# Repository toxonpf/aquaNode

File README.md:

# AquaNode website

React + TypeScript + Vite, React Router, React Three Fiber / Three.js and GSAP ScrollTrigger. Russian, English and Traditional Chinese (Taiwan) public interfaces; seven routes. Russian is the default. An icon-triggered language menu in the header and footer saves the selection and updates the interface without a reload. No contact form is configured.

## Run

Node 22.12+ (verified with Node 26) and npm:

```sh
npm install
npm run dev
```

Open the URL printed by Vite (normally http://127.0.0.1:5173).

```sh
npm run build
npm run preview
npx playwright test
```

Tests use Playwright Chromium (`npx playwright install chromium` if needed). An installed browser can be selected without editing the config:

```sh
PLAYWRIGHT_CHROMIUM_EXECUTABLE_PATH=/usr/bin/chromium npx playwright test
```

## Ocean styles

Open the browser developer console on the running site:

```js
oceanStyle(4)  // Select a style immediately, without reloading the scene.
oceanStyle(9)  // Return to the current ocean (default).
oceanStyle()   // List all styles with numbers, names and descriptions.
```

The choice is saved in this browser and survives reloads and navigation. The command is available on every page; the selected surface appears in the overview's 3D ocean. Static/reduced-motion illustrations remain static. Water, buoy motion and network links use the same selected wave profile. Invalid values throw a `RangeError` and leave the current choice unchanged.

| Number | Style | Version |
| --- | --- | --- |
| 1 | Original | Original fine sparkling ripples |
| 2 | Smooth | Softer surface before the depth refinements |
| 3 | Soft depth | Organic colour variation and soft highlights |
| 4 | Fine ripples | Previous lake-like directional ripples |
| 5 | Long swell | First long ocean swells |
| 6 | Broad foam | Long waves with wide foam patches |
| 7 | Crest ribbons | Narrow foam ribbons along crests |
| 8 | Textured crests | Four waves, deeper colour and broken foam |
| 9 | Ocean | Current six-wave ocean with large swells and sparse foam |

Preset definitions are in `src/features/ocean/scene/oceanStyles.ts`, the console command and saved choice in `src/features/ocean/scene/oceanStyle.ts`, shared CPU/GPU wave functions in `src/features/ocean/scene/ocean.ts`, and appearance variants in `src/features/ocean/scene/OceanSurface.tsx`. Historical variants reuse the current buoy model, rectangular float and underwater scene; the original style retains its historical circular waterline. Only the selected surface shader is compiled.

## Cursor styles

Switch immediately in the browser console; the selection is saved across pages and reloads:

```js
cursorStyle(0) // Native system cursor.
cursorStyle(1) // Water trail with animated arrows (default).
cursorStyle()  // Read the selected number.
```

The command is available on every page. Touch, reduced motion and forced colors retain native controls. The console store is in `src/features/cursor/cursorStyle.ts`; the pointer rendering is in `src/features/cursor/SiteCursor.tsx`.

## Future publication

Publish `dist/` as a static site after `npm run build`. Configure the host to serve `index.html` for application paths (`/about`, `/technology`, `/build`, `/journal`, `/team`); asset paths must serve the actual files. A Netlify-style `_redirects` file is included. No backend or secrets are required. Hosting and domain remain undecided; nothing has been published. Add the final absolute site URL and social preview image to the metadata when the domain is chosen.

## Editing

See the [project structure and editing map](docs/project-structure.md) for source folders, CSS order and test groups.

- `src/data/catalog.ts`: navigation, people and optional social links, resources, assembly steps, project updates, conceptual part descriptions.
- `src/main.tsx`: React startup; `src/app/App.tsx`: routes and page shell; `src/pages/`: page composition and English source phrases passed to `t()`.
- `src/data/content.ts`: localizes shared editorial records for the selected language.
- `src/features/i18n/i18n.ts` and `src/features/i18n/locales/ru*.ts` / `zh-TW.ts`: language selection, Russian copy and named placeholders. See [localization notes](docs/localization.md).
- `src/features/ocean/scene/Scene.tsx`: ocean rendering, lighting and camera transitions.
- `src/features/buoy/BuoyModel.tsx` and `src/features/buoy/BuoyDrawing.tsx`: lightweight 3D and static buoy illustrations, based on the supplied open-pisciculture reference.
- `src/features/ocean/story/BuoyAnnotation.tsx` and `src/features/buoy/buoyAnchors.ts`: the annotation's fixed attachment point, SVG arrow and damped bend. The 3D scene projects the lid point after applying the buoy's current wave transforms; only the bend has inertia, while the tip tracks exactly. The static illustration uses its corresponding SVG point.
- `src/features/ocean/story/SensorPanel.tsx`, `src/features/ocean/scene/Underwater.tsx` and `src/features/ocean/styles/sensors.css`: the underwater chapter, sensor explanations, projected probe controls, light and particles.
- `src/styles/base.css`: desktop and separately composed mobile layouts, reduced-motion rules.
- `public/resources/`: genuine supplied downloadable materials. Do not copy the entire engineering package into this public directory: it contains unapproved protocol details.
- `public/assets/`: supplied engineering images and licensed ocean recording.

New journal entries are objects in `updates`; leave dates undated when unknown. Team social links render only when a real `{ label, url }` item exists. Contacts and form work were explicitly deferred by the user; no email address or successful submission is fabricated.

## Design

The opening section is one full viewport of ocean viewed from above, with a cream and marine-blue buoy at its centre. A dark loading screen with a small spinner covers the scene until its first WebGL frame is rendered, then fades out over 900 ms to reveal the brighter ocean. The navigation sits over the water. One second after that reveal, “what is this?” fades in and a curved arrow draws toward the buoy. A moving line and downward arrow invite scrolling; both the annotation and cue link to the current project section. The rest of the overview remains available below while sections are refined individually.

The Three.js ocean uses an actual displaced mesh, analytic wave normals, reflected sky, sun glints and fine wind ripples. The buoy samples the same four directional swells as the water, so its height and tilt follow the surface. Wave parameters and the shared CPU/GPU equations are in `src/features/ocean/scene/ocean.ts`. Opening-section styles are in `src/features/ocean/styles/ocean.css`.

The opening has five chapters in one persistent canvas: the overhead surface, a close look at the buoy, and the probes below the water. Each distinct vertical wheel gesture, swipe or navigation key advances one adjacent chapter. Short anchors, 56–96 px apart, replace the empty viewport-length gaps. Further input is consumed until the camera and copy have settled and the current gesture has paused for 280 ms, preventing momentum from skipping a chapter. Leaving the last chapter returns to ordinary page scrolling; its remaining momentum is consumed until that gesture ends. Chapter links and the dive cue provide direct navigation. Pinch zoom, horizontal gestures and text/button input retain their normal controls. The underwater camera travels around and beneath the float; the background, underside of the water and light change with it. Text and its gradient appear together once the camera settles. The isolated pH, EC and temperature controls select a matching explanation, probe highlight and pulse colour. Moving labels attached to the probe array offer duplicate pointer controls; the stationary selector provides keyboard and screen-reader access. No live measurements are simulated. Reduced motion and unavailable WebGL retain all chapter navigation and sensor explanations with the static illustration.

No texture downloads or post-processing passes are used. The enclosure label is drawn locally on a small canvas. Animation runs only while the scene is visible and the browser tab is active. The secondary model renders on demand. Pending 3D uses a loading indicator rather than an SVG illustration. A static SVG is reserved for reduced motion, limited hardware, unavailable WebGL or a failed 3D download; those states leave loading immediately instead of waiting for a frame that cannot render. The buoy follows the open-pisciculture reference's rectangular float, central mast, upright enclosure and lower probe tube, with softened edges and an AquaNode finish. Its dimensions and details remain illustrative. Scrolling stays native.

## Evidence and unfinished content

Current engineering source: `AquaNode_R0.3_EC_pH_revC/`, dated 2 November 2026. revC is a freshwater bench configuration with experimental EC (SEN0244), temperature (DS18B20), and isolated pH (SEN0169-V2 → DFR0504 → ADS1115). The pH isolator uses a separate regulated bench supply; battery-powered pH and its energy budget are incomplete.

The supplied reports record 18 Python tests (15 EC model, 3 pH exporter), 166 schematic pins and 139 PCB pads compared across source files. These are source/software checks, not hardware evidence. Fifteen C++ pH assertions were not run. The ESP32 build attempt stopped during dependency download. Native ERC/DRC, physical calibration, shared-water tests and fabrication release remain pending. Real calibration coefficients and measured accuracy are not supplied. The presentation profile is simulation and is not used as hardware evidence.

`src/data/revisions/ec-ph-revc.json` is a website projection of these reports, with unknown outcomes kept null; it is not a supplied status file. `src/data/project.ts` exposes the current revision. RU/zh-TW revC copy is in `ru-revc.ts` and `zh-revc.ts`. Public summaries, status, evidence and attribution are under `public/resources/ec-ph-revc/`. Localized diagrams are generated by `scripts/design-architecture.mjs`. Firmware/protocol implementation is not added to web downloads. The supplied engineering directory is unchanged.

Historical revB downloads and diagrams remain at their existing URLs. Older R0.3 native checks and previous source counts are historical, not revC results. The independent Taiwan station archive and geographic map examples are not AquaNode field readings.

## Accessibility and loading

Model code is lazy-loaded, the secondary model waits for proximity to the viewport, and DPR is capped at 1.5. The hero animates only while visible in an active tab; secondary rendering uses demand mode. Reduced motion, data saver, limited reported memory, missing WebGL2 and lost contexts use a lightweight SVG view. Descriptions remain accessible without 3D. No automatic audio playback or audio download; one persistent toggle starts/stops the recording. Large imagery uses lazy loading. Native navigation, focus outlines, skip link, descriptive image alternatives and keyboard controls are present.

The 3D chunk still contains the Three.js renderer and is significantly larger than the core page. Users who request reduced motion or cannot use WebGL do not load it. Google Fonts uses display=swap with system fallbacks; the site is usable if fonts cannot load.

## Sources and licences

- Supplied `AquaNode_R0.3/`: README, Engineering, Purchase_and_test, Verification, BOM, Assembly and PCB drawings. Original directory is preserved. Public attribution: `public/resources/ATTRIBUTION.md`. New package documentation is CC BY 4.0; hardware CERN-OHL-P-2.0, with upstream notices in the original package.
- Award and historical context: https://thegeep.org/programs/youth-innovation-challenge/aquanode-team (checked 2026-10-21). Current user facts take precedence over its earlier capability description.
- Ocean audio: **Oceanwavescrushing.ogg**, Luftrum, 2008. https://commons.wikimedia.org/wiki/File:Oceanwavescrushing.ogg . Download: https://upload.wikimedia.org/wikipedia/commons/f/f1/Oceanwavescrushing.ogg . **CC BY 3.0**: https://creativecommons.org/licenses/by/3.0/ . Attribution and licence link appear in every page footer. The original file is unchanged; AquaNode applies a quieter mix and real-time underwater filtering. Playback is opt-in and limited to the five ocean chapters on the overview. Leaving the scene, changing page or hiding the tab fades and pauses it; returning resumes only if sound was enabled.
- Type: DM Sans and Manrope from Google Fonts, SIL Open Font License; https://fonts.google.com/specimen/DM+Sans and https://fonts.google.com/specimen/Manrope . Loaded from Google Fonts, not bundled.
- Design references reviewed: https://www.hut8.com (clear hierarchy and scale); https://15th.plus-ex.com (object-led reference, text access limited). https://encoder.digital/en was unavailable to the research tool; no claim of a completed visual review. No reference site's code or imagery was copied.
- Model and SVG fallback: authored for this website using the [open-pisciculture mechanical assembly and photographs](https://github.com/open-pisciculture/open-source-fish-farming-prototypes/tree/1ff67e96c81d22075cd6b9517ece5539700fd0e9/data-buoy-node) as visual references. The STEP assembly was reviewed; upstream meshes and photographs are not bundled. Source credits and adaptation details are in `public/resources/ATTRIBUTION.md`.

## Remaining user inputs

1. Real photographs of the working prototype and any existing full buoy assembly instructions (absent from the workspace).
2. Clarification of which board is used by the working buoy versus R0.3, and evidence the team wants to publish.
3. Real team portraits and contact addresses. Portrait slots and multiple contacts per person are ready; see [docs/team-contacts.md](docs/team-contacts.md). Unfilled contacts remain disabled.
4. Hosting and domain only when publication is requested.

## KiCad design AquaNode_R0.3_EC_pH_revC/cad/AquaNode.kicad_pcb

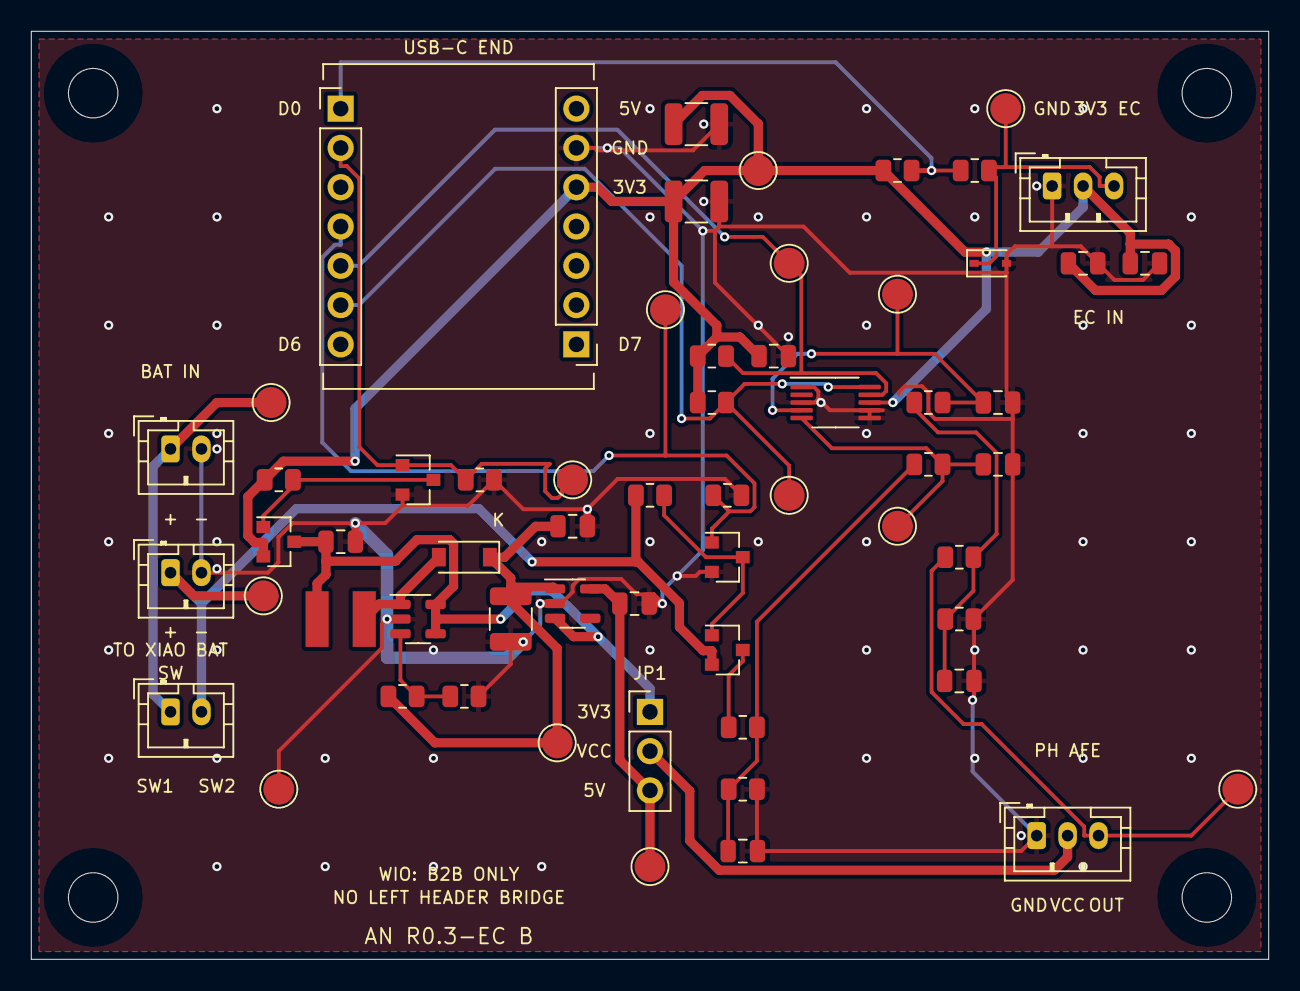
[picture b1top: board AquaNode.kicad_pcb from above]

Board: 2 copper layers, 80.0 x 60.0 mm, 65 parts (0 on the bottom side), 24 nets.

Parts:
C1, C13, C14, C15: 100nF; C_0805_2012Metric
C7, C10: 10uF; C_0805_2012Metric
C8, C17, C18: 22uF; C_1210_3225Metric
C9, C11, C12, C16: 1uF; C_0805_2012Metric
D1: Schottky 20V; D_SOD-123
D2: EC input ESD; D_SOD-323
H1, H2, H3, H4: M3 NPTH; MountingHole_3.2mm_M3
J1: XIAO_LEFT_D0..D6; PinHeader_1x07_P2.54mm_Vertical
J2: XIAO_RIGHT_D7..5V; PinHeader_1x07_P2.54mm_Vertical
J3: BATTERY + -; JST_PH_B2B-PH-K_1x02_P2.00mm_Vertical
J4: TO XIAO BAT PADS; JST_PH_B2B-PH-K_1x02_P2.00mm_Vertical
J5: SPST BATTERY SWITCH; JST_PH_B2B-PH-K_1x02_P2.00mm_Vertical
J7: EC G / 3V3-NO-CABLE / A; JST_PH_B3B-PH-K_1x03_P2.00mm_Vertical
J9: PH ISOLATED RETURN G / NC / A; JST_PH_B3B-PH-K_1x03_P2.00mm_Vertical
JP1: PH POWER 3V3 / 5V; PinHeader_1x03_P2.54mm_Vertical
L1: 10uH 1.4A sat; L_Bourns_SRN4018_Custom
Q1: P-MOS high side; SOT-23
Q2: N-MOS gate driver; SOT-23
Q3: Battery sense P-MOS; SOT-23
Q4: Battery sense driver; SOT-23
R1, R2: 4.7k; R_0805_2012Metric
R3: DNP - REMOVE 4.7k; R_0805_2012Metric
R4: 100R; R_0805_2012Metric
R5, R6, R18: 100k; R_0805_2012Metric
R7: 69.8k 0.1%; R_0805_2012Metric
R8: 20k 0.1%; R_0805_2012Metric
R9, R10: 49.9k 0.1%; R_0805_2012Metric
R11, R12: 100k 0.1%; R_0805_2012Metric
R15, R16: 1k; R_0805_2012Metric
R17: 1M; R_0805_2012Metric
TP1: VBAT_RAW; TestPoint_Pad_D2.0mm
TP2: VBAT; TestPoint_Pad_D2.0mm
TP3: 3V3; TestPoint_Pad_D2.0mm
TP4: BAT_EN; TestPoint_Pad_D2.0mm
TP5: 5V_PH; TestPoint_Pad_D2.0mm
TP6: GND; TestPoint_Pad_D2.0mm
TP7: I2C_SDA; TestPoint_Pad_D2.0mm
TP8: I2C_SCL; TestPoint_Pad_D2.0mm
TP9: EC_FILTERED; TestPoint_Pad_D2.0mm
TP10: PH_OUT; TestPoint_Pad_D2.0mm
TP11: PH_EN; TestPoint_Pad_D2.0mm
TP12: BOOST_RAW; TestPoint_Pad_D2.0mm
TP13: ADC_PH; TestPoint_Pad_D2.0mm
TP14: ADC_BAT; TestPoint_Pad_D2.0mm
U1: ADS1115; VSSOP-10_3x3mm_P0.5mm
U7: TPS61040; SOT-23-5
U8: 5V LDO; SOT-23-5

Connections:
3V3: C1.1, C15.1, C16.1, C17.1, C18.1, J2.5, J7.2, Q1.2, R1.1, R2.1, R3.1, R5.1, TP3.1, U1.8
5V_PH: C10.1, JP1.3, TP5.1, U8.5
ADC_BAT: C14.1, R16.2, TP14.1, U1.5
ADC_PH: C13.1, R15.2, TP13.1, U1.4
BAT_DIV: C12.1, R11.2, R12.1, R16.1
BAT_EN: J1.4, Q4.1, R18.1, TP4.1
BAT_GATE: Q3.1, Q4.3, R17.2
BAT_SENSE: Q3.3, R11.1
BOOST_FB: R7.2, R8.1, U7.3
BOOST_IN: C7.1, JP1.1, L1.1, Q1.3, U7.4, U7.5, U8.3
BOOST_RAW: C8.1, C9.1, D1.1, R7.1, TP12.1, U8.1
BOOST_SW: D1.2, L1.2, U7.1
EC_ADC: J1.1, R3.2, R4.1
EC_FILTERED: D2.1, J7.3, R4.2, TP9.1
GND: C1.2, C7.2, C8.2, C9.2, C10.2, C11.2, C12.2, C13.2, C14.2, C15.2, C16.2, C17.2, C18.2, D2.2, J2.6, J3.2, J4.2, J7.1, J9.1, Q2.2, Q4.2, R6.2, R8.2, R10.2, R12.2, R18.2, TP6.1, U1.1, U1.3, U1.6, U1.7, U7.2, U8.2
I2C_SCL: J1.6, R2.2, TP8.1, U1.10
I2C_SDA: J1.5, R1.2, TP7.1, U1.9
PH_DIV: C11.1, R9.2, R10.1, R15.1
PH_EN: J1.2, Q2.1, R6.1, TP11.1
PH_GATE: Q1.1, Q2.3, R5.2
PH_OUT: J9.3, R9.1, TP10.1
PH_SUPPLY: J9.2, JP1.2
VBAT: J4.1, J5.2, Q3.2, R17.1, TP2.1
VBAT_RAW: J3.1, J5.1, TP1.1

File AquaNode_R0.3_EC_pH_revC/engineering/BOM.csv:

reference,value,mpn,location,fit,notes
J1,XIAO_LEFT_D0..D6,Samtec TSW-107-07-G-S,carrier,FIT,D0/GPIO1 EC ADC; D6/GPIO43 DS18B20. USB CDC only; do not use UART0 TX.
J2,XIAO_RIGHT_D7..5V,Samtec TSW-107-07-G-S,carrier,FIT,Pin 7 at USB end. USB_DEV is XIAO 5V/VBUS; never inject boosted power.
J3,BATTERY + -,B2B-PH-K-S(LF)(SN),carrier,FIT,Protected 1S pack only. Verify actual plug polarity; JST housing does not guarantee polarity.
J4,TO XIAO BAT PADS,B2B-PH-K-S(LF)(SN),carrier,FIT,Pigtail soldered to XIAO underside BAT+/BAT- pads. Not to 3V3 or 5V.
J5,SPST BATTERY SWITCH,B2B-PH-K-S(LF)(SN),carrier,FIT,External two-wire SPST. USB remains a service power source; unplug USB for full shutdown.
J7,EC G / 3V3-NO-CABLE / A,B3B-PH-K-S(LF)(SN),carrier,FIT,"Pin 2 remains 3V3 copper. Depopulate and insulate cable contact 2. SEN0244 VCC comes from TP5, never bridge TP5 to J7.2."
J9,PH ISOLATED RETURN G / NC / A,B3B-PH-K-S(LF)(SN),carrier,FIT,J9.1 MCU GND; J9.2 NO CABLE CONTACT; J9.3 DFR0504 MCU A. JP1 shunt removed. SEN0169-V2 connects ONLY to isolated SEN side of M4.
JP1,PH POWER 3V3 / 5V,Samtec TSW-103-07-G-S,carrier,FIT,NO SHUNT in revC. Both 1-2 and 2-3 forbidden for this harness; J9.2 has no cable contact.
U1,ADS1115,ADS1115IDGSR,carrier,FIT,"0x48; AIN0 pH via original 49.9k/49.9k divider; single-shot +/-4.096V, 16 SPS. AIN2/3 grounded."
U7,TPS61040,TPS61040DBVR,carrier,FIT,EN tied to switched input to avoid EN > VIN during power-off.
U8,5V LDO,TPS7A2050PDBVR,carrier,FIT,EN follows switched boost input; check startup and shutdown transients.
Q1,P-MOS high side,AO3401A,carrier,FIT,
Q2,N-MOS gate driver,"2N7002,215",carrier,FIT,
D1,Schottky 20V,MBR0520LT1G,carrier,FIT,
D2,EC input ESD,"PESD3V3S1BA,115",carrier,FIT,"ESD only; leakage/clamp require bench verification, not powered-off isolation."
L1,10uH 1.4A sat,SRN4018-100M,carrier,FIT,"Semi-shielded; land pattern from Bourns recommended layout, still requires CAD review."
R1,4.7k,CRCW08054K70FKEA,carrier,FIT,
R2,4.7k,CRCW08054K70FKEA,carrier,FIT,
R3,DNP - REMOVE 4.7k,CRCW08054K70FKEA,carrier,DNP,Mandatory removal; otherwise biases EC analog input.
R4,100R,CRCW0805100RFKEA,carrier,FIT,
R5,100k,CRCW0805100KFKEA,carrier,FIT,
R6,100k,CRCW0805100KFKEA,carrier,FIT,
R7,69.8k 0.1%,RNCS0805BKE69K8,carrier,FIT,
R8,20k 0.1%,RT0805BRD0720KL,carrier,FIT,
R9,49.9k 0.1%,RT0805BRD0749K9L,carrier,FIT,
R10,49.9k 0.1%,RT0805BRD0749K9L,carrier,FIT,
R11,100k 0.1%,RT0805BRD07100KL,carrier,FIT,
R12,100k 0.1%,RT0805BRD07100KL,carrier,FIT,
R15,1k,CRCW08051K00FKEA,carrier,FIT,
R16,1k,CRCW08051K00FKEA,carrier,FIT,
C1,100nF,GRM21BR71H104KA01L,carrier,FIT,
C7,10uF,GRM21BR61A106KE19L,carrier,FIT,
C8,22uF,GRM32ER71C226KEA8L,carrier,FIT,
C9,1uF,GRM21BR71E105KA99L,carrier,FIT,
C10,10uF,GRM21BR61A106KE19L,carrier,FIT,
C11,1uF,GRM21BR71E105KA99L,carrier,FIT,
C12,1uF,GRM21BR71E105KA99L,carrier,FIT,
C13,100nF,GRM21BR71H104KA01L,carrier,FIT,
C14,100nF,GRM21BR71H104KA01L,carrier,FIT,
C15,100nF,GRM21BR71H104KA01L,carrier,FIT,
C16,1uF,GRM21BR71E105KA99L,carrier,FIT,
C17,22uF,GRM32ER71C226KEA8L,carrier,FIT,
C18,22uF,GRM32ER71C226KEA8L,carrier,FIT,
TP1,VBAT_RAW,PCB copper pad,carrier,FIT,No purchased component.
TP2,VBAT,PCB copper pad,carrier,FIT,No purchased component.
TP3,3V3,PCB copper pad,carrier,FIT,No purchased component.
TP4,BAT_EN,PCB copper pad,carrier,FIT,No purchased component.
TP5,5V_PH,PCB copper pad,carrier,FIT,No purchased component.
TP6,GND,PCB copper pad,carrier,FIT,No purchased component.
TP7,I2C_SDA,PCB copper pad,carrier,FIT,No purchased component.
TP8,I2C_SCL,PCB copper pad,carrier,FIT,No purchased component.
TP9,EC_FILTERED,PCB copper pad,carrier,FIT,No purchased component.
TP10,PH_OUT,PCB copper pad,carrier,FIT,No purchased component.
TP11,PH_EN,PCB copper pad,carrier,FIT,No purchased component.
TP12,BOOST_RAW,PCB copper pad,carrier,FIT,No purchased component.
TP13,ADC_PH,PCB copper pad,carrier,FIT,No purchased component.
TP14,ADC_BAT,PCB copper pad,carrier,FIT,No purchased component.
H1,M3 NPTH,M3 nylon standoff,carrier,FIT,3.2mm drill; copper keepout radius 3.2mm.
H2,M3 NPTH,M3 nylon standoff,carrier,FIT,3.2mm drill; copper keepout radius 3.2mm.
H3,M3 NPTH,M3 nylon standoff,carrier,FIT,3.2mm drill; copper keepout radius 3.2mm.
H4,M3 NPTH,M3 nylon standoff,carrier,FIT,3.2mm drill; copper keepout radius 3.2mm.
Q3,Battery sense P-MOS,AO3401A,carrier,FIT,
Q4,Battery sense driver,"2N7002,215",carrier,FIT,
R17,1M,CRCW08051M00FKEA,carrier,FIT,
R18,100k,CRCW0805100KFKEA,carrier,FIT,
M1,DFRobot SEN0244,,external,FIT,
R19,4.7k,,external,FIT,
R20,100R,,external,FIT,
D3,PESD3V3S1BA,,external,FIT,
M2,Existing DS18B20 probe,,external,FIT,
R21,1k,,external,FIT,
C19,100nF,,external,FIT,
M3,DFRobot SEN0169-V2 pH kit,SEN0169-V2,external,FIT,BNC electrode connects to this AFE only; no main-ground connection on SEN side.
M4,DFRobot DFR0504 pH isolation,DFR0504,external,FIT,"Pin numbers are LOGICAL, not manufacturer physical numbering. Wire by printed MCU/SEN and -/+/A labels. External regulated 5.0 +/-0.1V >=0.5A bench supply; never TP5 or XIAO 5V."
PS1,Bench regulated 5.00V +/-0.10V >=0.5A,LAB_SUPPLY_REQUIREMENT,external,FIT,Bench equipment; separate from XIAO USB. Keep output OFF until MCU/ADS1115 are powered; OFF first during shutdown. No autonomous battery regulator selected.
MODULE1,XIAO ESP32S3 + Wio SX1262,Seeed 102010611,module,FIT,Radio unused in bench firmware
PACK1,Protected 1S Li-ion,TBD,power,TBD,Capacity and autonomous pH power regulator not selected

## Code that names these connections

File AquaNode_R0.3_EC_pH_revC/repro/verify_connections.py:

"""Read actual schematic wires/pin positions and PCB pads; not native ERC/DRC."""
from inspect_local import ROOT, parse, child, children
import json, math, zipfile, hashlib

def ref(x):return next((p[2] for p in children(x,'property') if p[1]=='Reference'),None)
def pos(x):return tuple(round(float(v),5) for v in child(x,'at')[1:3])
d=json.loads((ROOT/'design.json').read_text())
s=parse((ROOT/'cad/AquaNode.kicad_sch').read_text());p=parse((ROOT/'cad/AquaNode.kicad_pcb').read_text())
syms={ref(x):x for x in children(s,'symbol')};fps={ref(x):x for x in children(p,'footprint')}
libs={x[1]:x for x in children(child(s,'lib_symbols'),'symbol')}
graph={};labels={}
for w in children(s,'wire'):
    pts=child(w,'pts');a=tuple(round(float(v),5) for v in pts[1][1:3]);b=tuple(round(float(v),5) for v in pts[2][1:3])
    graph.setdefault(a,set()).add(b);graph.setdefault(b,set()).add(a)
for x in children(s,'label'):labels.setdefault(pos(x),set()).add(x[1])
def nets_at(pt):
    seen=set();pending=[pt];out=set()
    while pending:
        n=pending.pop()
        if n in seen:continue
        seen.add(n);out.update(labels.get(n,set()));pending.extend(graph.get(n,set())-seen)
    return out
errors=[];pins=[];pads=0
for c in d['components']+d['external_components']:
    if not c['pins']:continue
    symbol=syms[c['ref']];at=child(symbol,'at');x,y,angle=map(float,at[1:4]);a=math.radians(angle)
    ps=[pin for u in children(libs[child(symbol,'lib_id')[1]],'symbol') for pin in children(u,'pin')]
    found=set()
    for pin in ps:
        num=child(pin,'number')[1];found.add(num)
        px,py=map(float,child(pin,'at')[1:3]);xy=(round(x+px*math.cos(a)-py*math.sin(a),5),round(y-px*math.sin(a)-py*math.cos(a),5))
        actual=nets_at(xy);expect=c['pins'].get(num)
        if num not in c['pins'] or (actual!={expect} if expect else bool(actual)):
            errors.append([c['ref'],num,expect,sorted(actual)])
        pins.append({'reference':c['ref'],'pin':num,'net':expect,'xy':xy,'actual_labels':sorted(actual)})
    if found!=set(c['pins']):errors.append(['missing_or_extra_pins',c['ref']])
    if c['ref'] in fps:
        for pad in children(fps[c['ref']],'pad'):
            if not pad[1]:continue
            net=child(pad,'net');actual=net[2] if net else None;pads+=1
            if actual!=c['pins'].get(pad[1]):errors.append(['PCB',c['ref'],pad[1],actual,c['pins'].get(pad[1])])
assert not errors,json.dumps(errors,indent=2)
b={c['ref']:c for c in d['components']+d['external_components']}
assert b['R3']['dnp'] and child(syms['R3'],'dnp')[1]=='yes' and 'dnp' in child(fps['R3'],'attr')
assert b['M3']['pins']=={'1':'PH_ISO_GND','2':'PH_ISO_5V','3':'PH_ISO_OUT'}
assert b['M4']['pins']=={'1':'GND','2':'PH_EXT_5V','3':'PH_OUT','4':'PH_ISO_GND','5':'PH_ISO_5V','6':'PH_ISO_OUT'}
assert b['J9']['pins']=={'1':'GND','2':'PH_SUPPLY','3':'PH_OUT'}
assert b['U1']['pins']['4']=='ADC_PH' and b['U1']['pins']['6']==b['U1']['pins']['7']=='GND'
assert b['R9']['pins']=={'1':'PH_OUT','2':'PH_DIV'} and b['R10']['pins']=={'1':'PH_DIV','2':'GND'}
assert b['R15']['pins']=={'1':'PH_DIV','2':'ADC_PH'}
assert b['J1']['pins']['5']=='I2C_SDA' and b['J1']['pins']['6']=='I2C_SCL'
isolated={'PH_ISO_GND','PH_ISO_5V','PH_ISO_OUT'}
assert all(c['ref'] in ('M3','M4') for c in d['components']+d['external_components'] if isolated & set(c['pins'].values()))
with zipfile.ZipFile(ROOT/'history/original_revB.zip') as z:
    old=parse(z.read('AquaNode_R0.3_EC_revB/cad/AquaNode.kicad_pcb').decode())
    oldfps={ref(x):x for x in children(old,'footprint')}
    for kind in ('segment','via','zone','gr_line','gr_arc'):assert children(old,kind)==children(p,kind),kind
    for name,f in fps.items():
        assert child(f,'at')==child(oldfps[name],'at')
        assert children(f,'pad')==children(oldfps[name],'pad')
# Divider worst case with 0.1% resistors; never mistake PGA range for input supply tolerance.
ratio_max=(49900*1.001)/(49900*.999+49900*1.001)
max_adc=5.1*ratio_max
assert max_adc<3.3
result={'scope':'source connectivity verification, NOT native ERC/DRC or hardware testing',
 'schematic_pins_checked':len(pins),'pcb_pads_checked':pads,'schematic_design_agreement':True,
 'pcb_design_agreement':True,'carrier_copper_and_pad_placement_unchanged_from_revB':True,
 'pH_isolated_nets_separate_in_source':True,'R3_DNP':True,
 'maximum_pH_ADC_V_assuming_5V1_isolator_output':max_adc,
 'JP1_and_J9_2_harness_omission':'assembly instruction; cannot verify physical wiring remotely',
 'native_erc':'NOT_RUN','native_drc':'NOT_RUN','hardware_tests':'NOT_RUN',
 'limitations':['coordinate graph checks wire endpoints and labels; not KiCad native connectivity engine',
 'no footprint/datasheet audit of every inherited component','power and shutdown transients unmeasured']}
(ROOT/'checks/connection_check.json').write_text(json.dumps(result,ensure_ascii=False,indent=2),encoding='utf8')
(ROOT/'checks/pin_by_pin.json').write_text(json.dumps(pins,ensure_ascii=False,indent=2),encoding='utf8')
print(json.dumps(result,ensure_ascii=False,indent=2))
